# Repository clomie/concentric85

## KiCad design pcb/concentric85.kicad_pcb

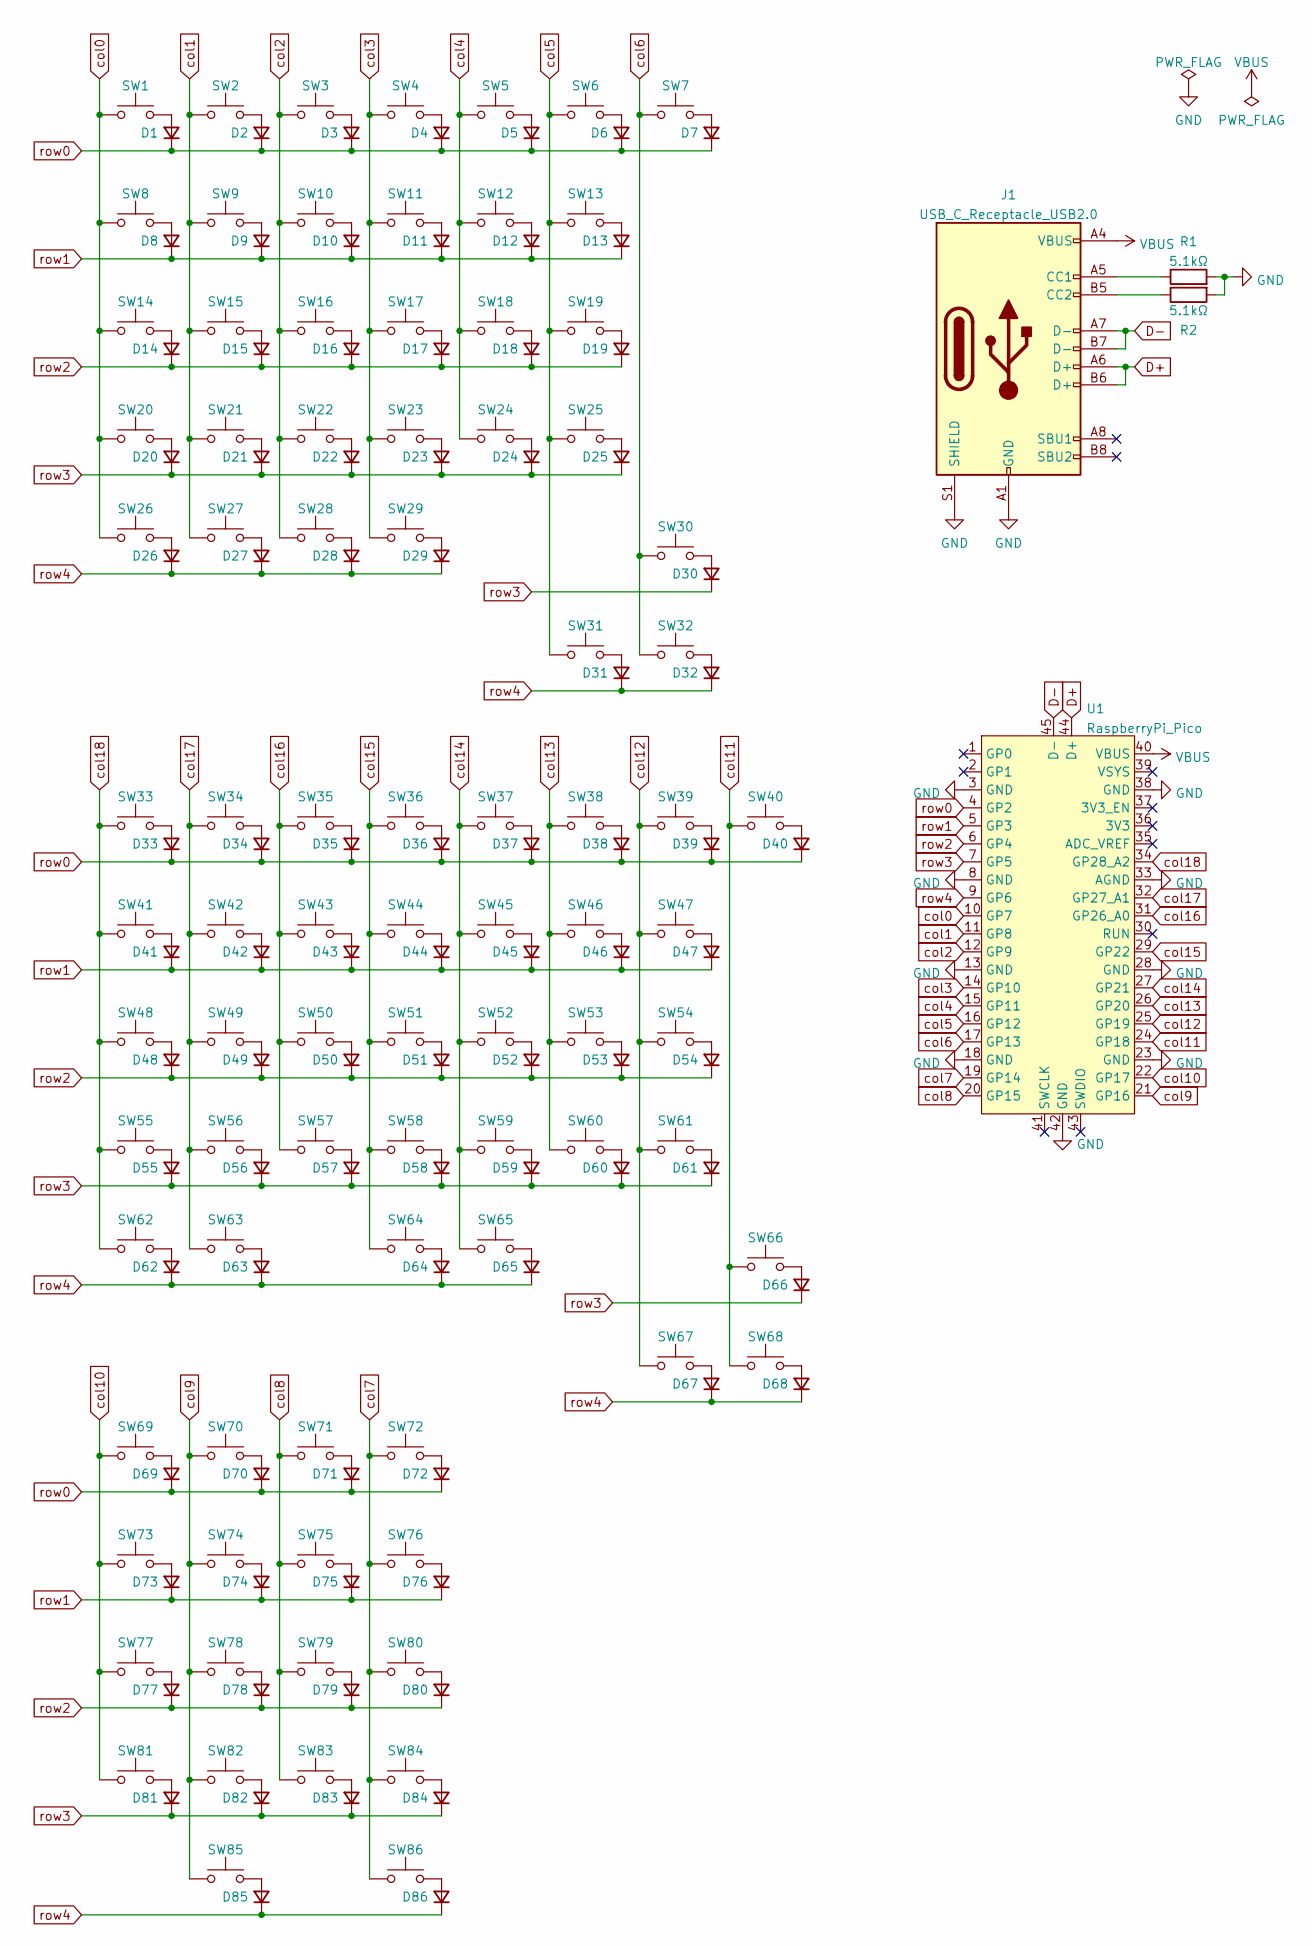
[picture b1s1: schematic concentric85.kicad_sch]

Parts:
D1, D2, D3, D4, D5, D6, D7, D8, D9, D10, D11, D12, D13, D14, D15, D16, D17, D18, D19, D20, D21, D22, D23, D24, D25, D26, D27, D28, D29, D30, D31, D32, D33, D34, D35, D36, D37, D38, D39, D40, D41, D42, D43, D44, D45, D46, D47, D48, D49, D50, D51, D52, D53, D54, D55, D56, D57, D58, D59, D60, D61, D62, D63, D64, D65, D66, D67, D68, D69, D70, D71, D72, D73, D74, D75, D76, D77, D78, D79, D80, D81, D82, D83, D84, D85, D86: D_Small; D3_SMD
J1: USB_C_Receptacle_USB2.0; USB_C_Receptacle_GCT_USB4085
R1, R2: 5.1kΩ; R_0805_2012Metric_Pad1.20x1.40mm_HandSolder
SW1, SW2, SW3, SW4, SW5, SW6, SW7, SW9, SW10, SW11, SW12, SW13, SW15, SW16, SW17, SW18, SW19, SW21, SW22, SW23, SW24, SW25, SW27, SW30, SW31, SW32, SW33, SW34, SW35, SW36, SW37, SW38, SW39, SW40, SW41, SW42, SW43, SW44, SW45, SW46, SW47, SW48, SW49, SW50, SW51, SW52, SW53, SW54, SW55, SW56, SW57, SW58, SW59, SW60, SW61, SW62, SW66, SW67, SW68, SW69, SW70, SW71, SW72, SW73, SW74, SW75, SW76, SW77, SW78, SW79, SW80, SW81, SW82, SW83, SW84, SW85: SW_Push; MX_1.00u_Hotswap
SW8, SW26, SW28, SW29, SW63, SW64, SW65: SW_Push; MX_1.50u_Hotswap
SW14: SW_Push; MX_1.75u_Hotswap
SW20: SW_Push; MX_2.25u_Hotswap
SW86: SW_Push; MX_2.00u_Hotswap
U1: RaspberryPi_Pico

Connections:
D+: J1.A6 (D+), J1.B6 (D+), U1.44 (D+)
D-: J1.A7 (D-), J1.B7 (D-), U1.45 (D-)
GND: J1.A1 (GND), J1.A12 (GND), J1.B1 (GND), J1.B12 (GND), J1.S1 (SHIELD), R1.2, R2.2, U1.3 (GND), U1.8 (GND), U1.13 (GND), U1.18 (GND), U1.23 (GND), U1.28 (GND), U1.33 (AGND), U1.38 (GND), U1.42 (GND)
unnamed: D1.2 (A), SW1.2
unnamed: D2.2 (A), SW2.2
unnamed: D3.2 (A), SW3.2
unnamed: D4.2 (A), SW4.2
unnamed: D5.2 (A), SW5.2
unnamed: D6.2 (A), SW6.2
unnamed: D7.2 (A), SW7.2
unnamed: D8.2 (A), SW8.2
unnamed: D9.2 (A), SW9.2
unnamed: D10.2 (A), SW10.2
unnamed: D11.2 (A), SW11.2
unnamed: D12.2 (A), SW12.2
unnamed: D13.2 (A), SW13.2
unnamed: D14.2 (A), SW14.2
unnamed: D15.2 (A), SW15.2
unnamed: D16.2 (A), SW16.2
unnamed: D17.2 (A), SW17.2
unnamed: D18.2 (A), SW18.2
unnamed: D19.2 (A), SW19.2
unnamed: D20.2 (A), SW20.2
unnamed: D21.2 (A), SW21.2
unnamed: D22.2 (A), SW22.2
unnamed: D23.2 (A), SW23.2
unnamed: D24.2 (A), SW24.2
unnamed: D25.2 (A), SW25.2
unnamed: D26.2 (A), SW26.2
unnamed: D27.2 (A), SW27.2
unnamed: D28.2 (A), SW28.2
unnamed: D29.2 (A), SW29.2
unnamed: D30.2 (A), SW30.2
unnamed: D31.2 (A), SW31.2
unnamed: D32.2 (A), SW32.2
unnamed: D33.2 (A), SW33.2
unnamed: D34.2 (A), SW34.2
unnamed: D35.2 (A), SW35.2
unnamed: D36.2 (A), SW36.2
unnamed: D37.2 (A), SW37.2
unnamed: D38.2 (A), SW38.2
unnamed: D39.2 (A), SW39.2
unnamed: D40.2 (A), SW40.2
unnamed: D41.2 (A), SW41.2
unnamed: D42.2 (A), SW42.2
unnamed: D43.2 (A), SW43.2
unnamed: D44.2 (A), SW44.2
unnamed: D45.2 (A), SW45.2
unnamed: D46.2 (A), SW46.2
unnamed: D47.2 (A), SW47.2
unnamed: D48.2 (A), SW48.2
unnamed: D49.2 (A), SW49.2
unnamed: D50.2 (A), SW50.2
unnamed: D51.2 (A), SW51.2
unnamed: D52.2 (A), SW52.2
unnamed: D53.2 (A), SW53.2
unnamed: D54.2 (A), SW54.2
unnamed: D55.2 (A), SW55.2
unnamed: D56.2 (A), SW56.2
unnamed: D57.2 (A), SW57.2
unnamed: D58.2 (A), SW58.2
unnamed: D59.2 (A), SW59.2
unnamed: D60.2 (A), SW60.2
unnamed: D61.2 (A), SW61.2
unnamed: D62.2 (A), SW62.2
unnamed: D63.2 (A), SW63.2
unnamed: D64.2 (A), SW64.2
unnamed: D65.2 (A), SW65.2
unnamed: D66.2 (A), SW66.2
unnamed: D67.2 (A), SW67.2
unnamed: D68.2 (A), SW68.2
unnamed: D69.2 (A), SW69.2
unnamed: D70.2 (A), SW70.2
unnamed: D71.2 (A), SW71.2
unnamed: D72.2 (A), SW72.2
unnamed: D73.2 (A), SW73.2
unnamed: D74.2 (A), SW74.2
unnamed: D75.2 (A), SW75.2
unnamed: D76.2 (A), SW76.2
unnamed: D77.2 (A), SW77.2
unnamed: D78.2 (A), SW78.2
unnamed: D79.2 (A), SW79.2
unnamed: D80.2 (A), SW80.2
unnamed: D81.2 (A), SW81.2
unnamed: D82.2 (A), SW82.2
unnamed: D83.2 (A), SW83.2
unnamed: D84.2 (A), SW84.2
unnamed: D85.2 (A), SW85.2
unnamed: D86.2 (A), SW86.2
unnamed: J1.A5 (CC1), R1.1
unnamed: J1.B5 (CC2), R2.1
VBUS: J1.A4 (VBUS), J1.A9 (VBUS), J1.B4 (VBUS), J1.B9 (VBUS), U1.40 (VBUS)
col0: SW1.1, SW8.1, SW14.1, SW20.1, SW26.1, U1.10 (GP7)
col1: SW2.1, SW9.1, SW15.1, SW21.1, SW27.1, U1.11 (GP8)
col2: SW3.1, SW10.1, SW16.1, SW22.1, SW28.1, U1.12 (GP9)
col3: SW4.1, SW11.1, SW17.1, SW23.1, SW29.1, U1.14 (GP10)
col4: SW5.1, SW12.1, SW18.1, SW24.1, U1.15 (GP11)
col5: SW6.1, SW13.1, SW19.1, SW25.1, SW31.1, U1.16 (GP12)
col6: SW7.1, SW30.1, SW32.1, U1.17 (GP13)
col7: SW72.1, SW76.1, SW80.1, SW84.1, SW86.1, U1.19 (GP14)
col8: SW71.1, SW75.1, SW79.1, SW83.1, U1.20 (GP15)
col9: SW70.1, SW74.1, SW78.1, SW82.1, SW85.1, U1.21 (GP16)
col10: SW69.1, SW73.1, SW77.1, SW81.1, U1.22 (GP17)
col11: SW40.1, SW66.1, SW68.1, U1.24 (GP18)
col12: SW39.1, SW47.1, SW54.1, SW61.1, SW67.1, U1.25 (GP19)
col13: SW38.1, SW46.1, SW53.1, SW60.1, U1.26 (GP20)
col14: SW37.1, SW45.1, SW52.1, SW59.1, SW65.1, U1.27 (GP21)
col15: SW36.1, SW44.1, SW51.1, SW58.1, SW64.1, U1.29 (GP22)
col16: SW35.1, SW43.1, SW50.1, SW57.1, U1.31 (GP26_A0)
col17: SW34.1, SW42.1, SW49.1, SW56.1, SW63.1, U1.32 (GP27_A1)
col18: SW33.1, SW41.1, SW48.1, SW55.1, SW62.1, U1.34 (GP28_A2)
row0: D1.1 (K), D2.1 (K), D3.1 (K), D4.1 (K), D5.1 (K), D6.1 (K), D7.1 (K), D33.1 (K), D34.1 (K), D35.1 (K), D36.1 (K), D37.1 (K), D38.1 (K), D39.1 (K), D40.1 (K), D69.1 (K), D70.1 (K), D71.1 (K), D72.1 (K), U1.4 (GP2)
row1: D8.1 (K), D9.1 (K), D10.1 (K), D11.1 (K), D12.1 (K), D13.1 (K), D41.1 (K), D42.1 (K), D43.1 (K), D44.1 (K), D45.1 (K), D46.1 (K), D47.1 (K), D73.1 (K), D74.1 (K), D75.1 (K), D76.1 (K), U1.5 (GP3)
row2: D14.1 (K), D15.1 (K), D16.1 (K), D17.1 (K), D18.1 (K), D19.1 (K), D48.1 (K), D49.1 (K), D50.1 (K), D51.1 (K), D52.1 (K), D53.1 (K), D54.1 (K), D77.1 (K), D78.1 (K), D79.1 (K), D80.1 (K), U1.6 (GP4)
row3: D20.1 (K), D21.1 (K), D22.1 (K), D23.1 (K), D24.1 (K), D25.1 (K), D30.1 (K), D55.1 (K), D56.1 (K), D57.1 (K), D58.1 (K), D59.1 (K), D60.1 (K), D61.1 (K), D66.1 (K), D81.1 (K), D82.1 (K), D83.1 (K), D84.1 (K), U1.7 (GP5)
row4: D26.1 (K), D27.1 (K), D28.1 (K), D29.1 (K), D31.1 (K), D32.1 (K), D62.1 (K), D63.1 (K), D64.1 (K), D65.1 (K), D67.1 (K), D68.1 (K), D85.1 (K), D86.1 (K), U1.9 (GP6)

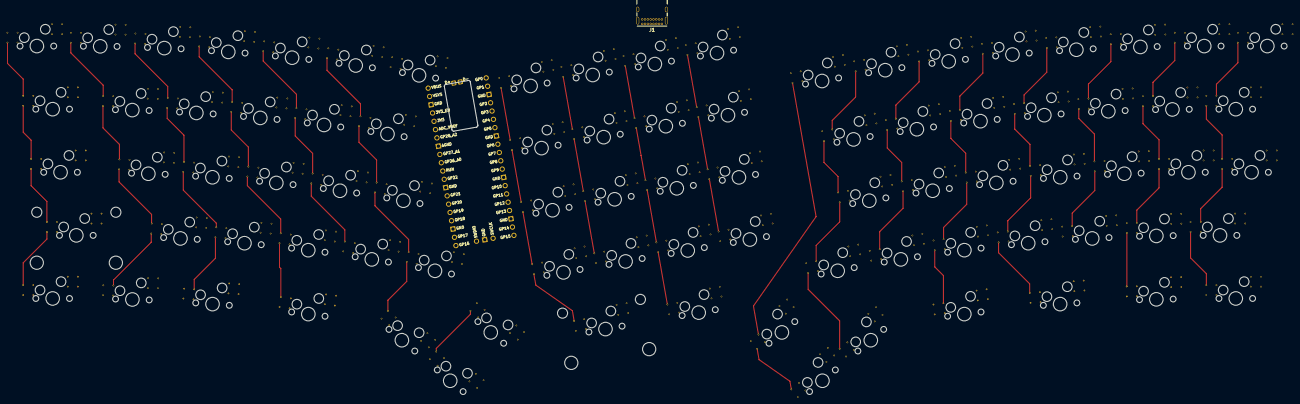
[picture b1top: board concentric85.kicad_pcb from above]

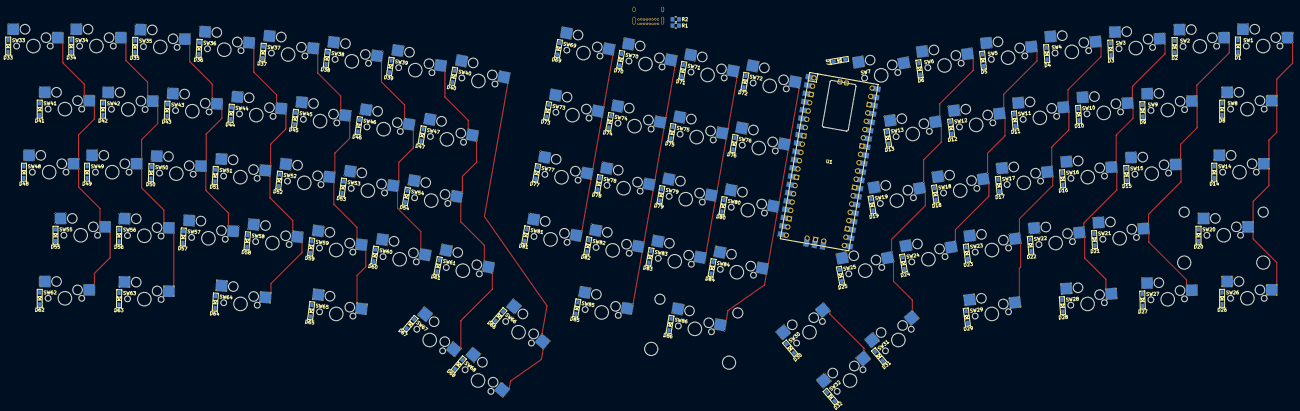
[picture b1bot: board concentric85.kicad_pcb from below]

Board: 2 copper layers, 176 parts (3 on the bottom side), 116 nets.

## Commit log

2021-11-28 Add README
2021-11-28 Add key layout
2022-01-10 Add generated key layout image
2022-01-10 Add gitignore file
2022-01-10 Add KiCAD files, completed schematics.
2024-01-08 backup
